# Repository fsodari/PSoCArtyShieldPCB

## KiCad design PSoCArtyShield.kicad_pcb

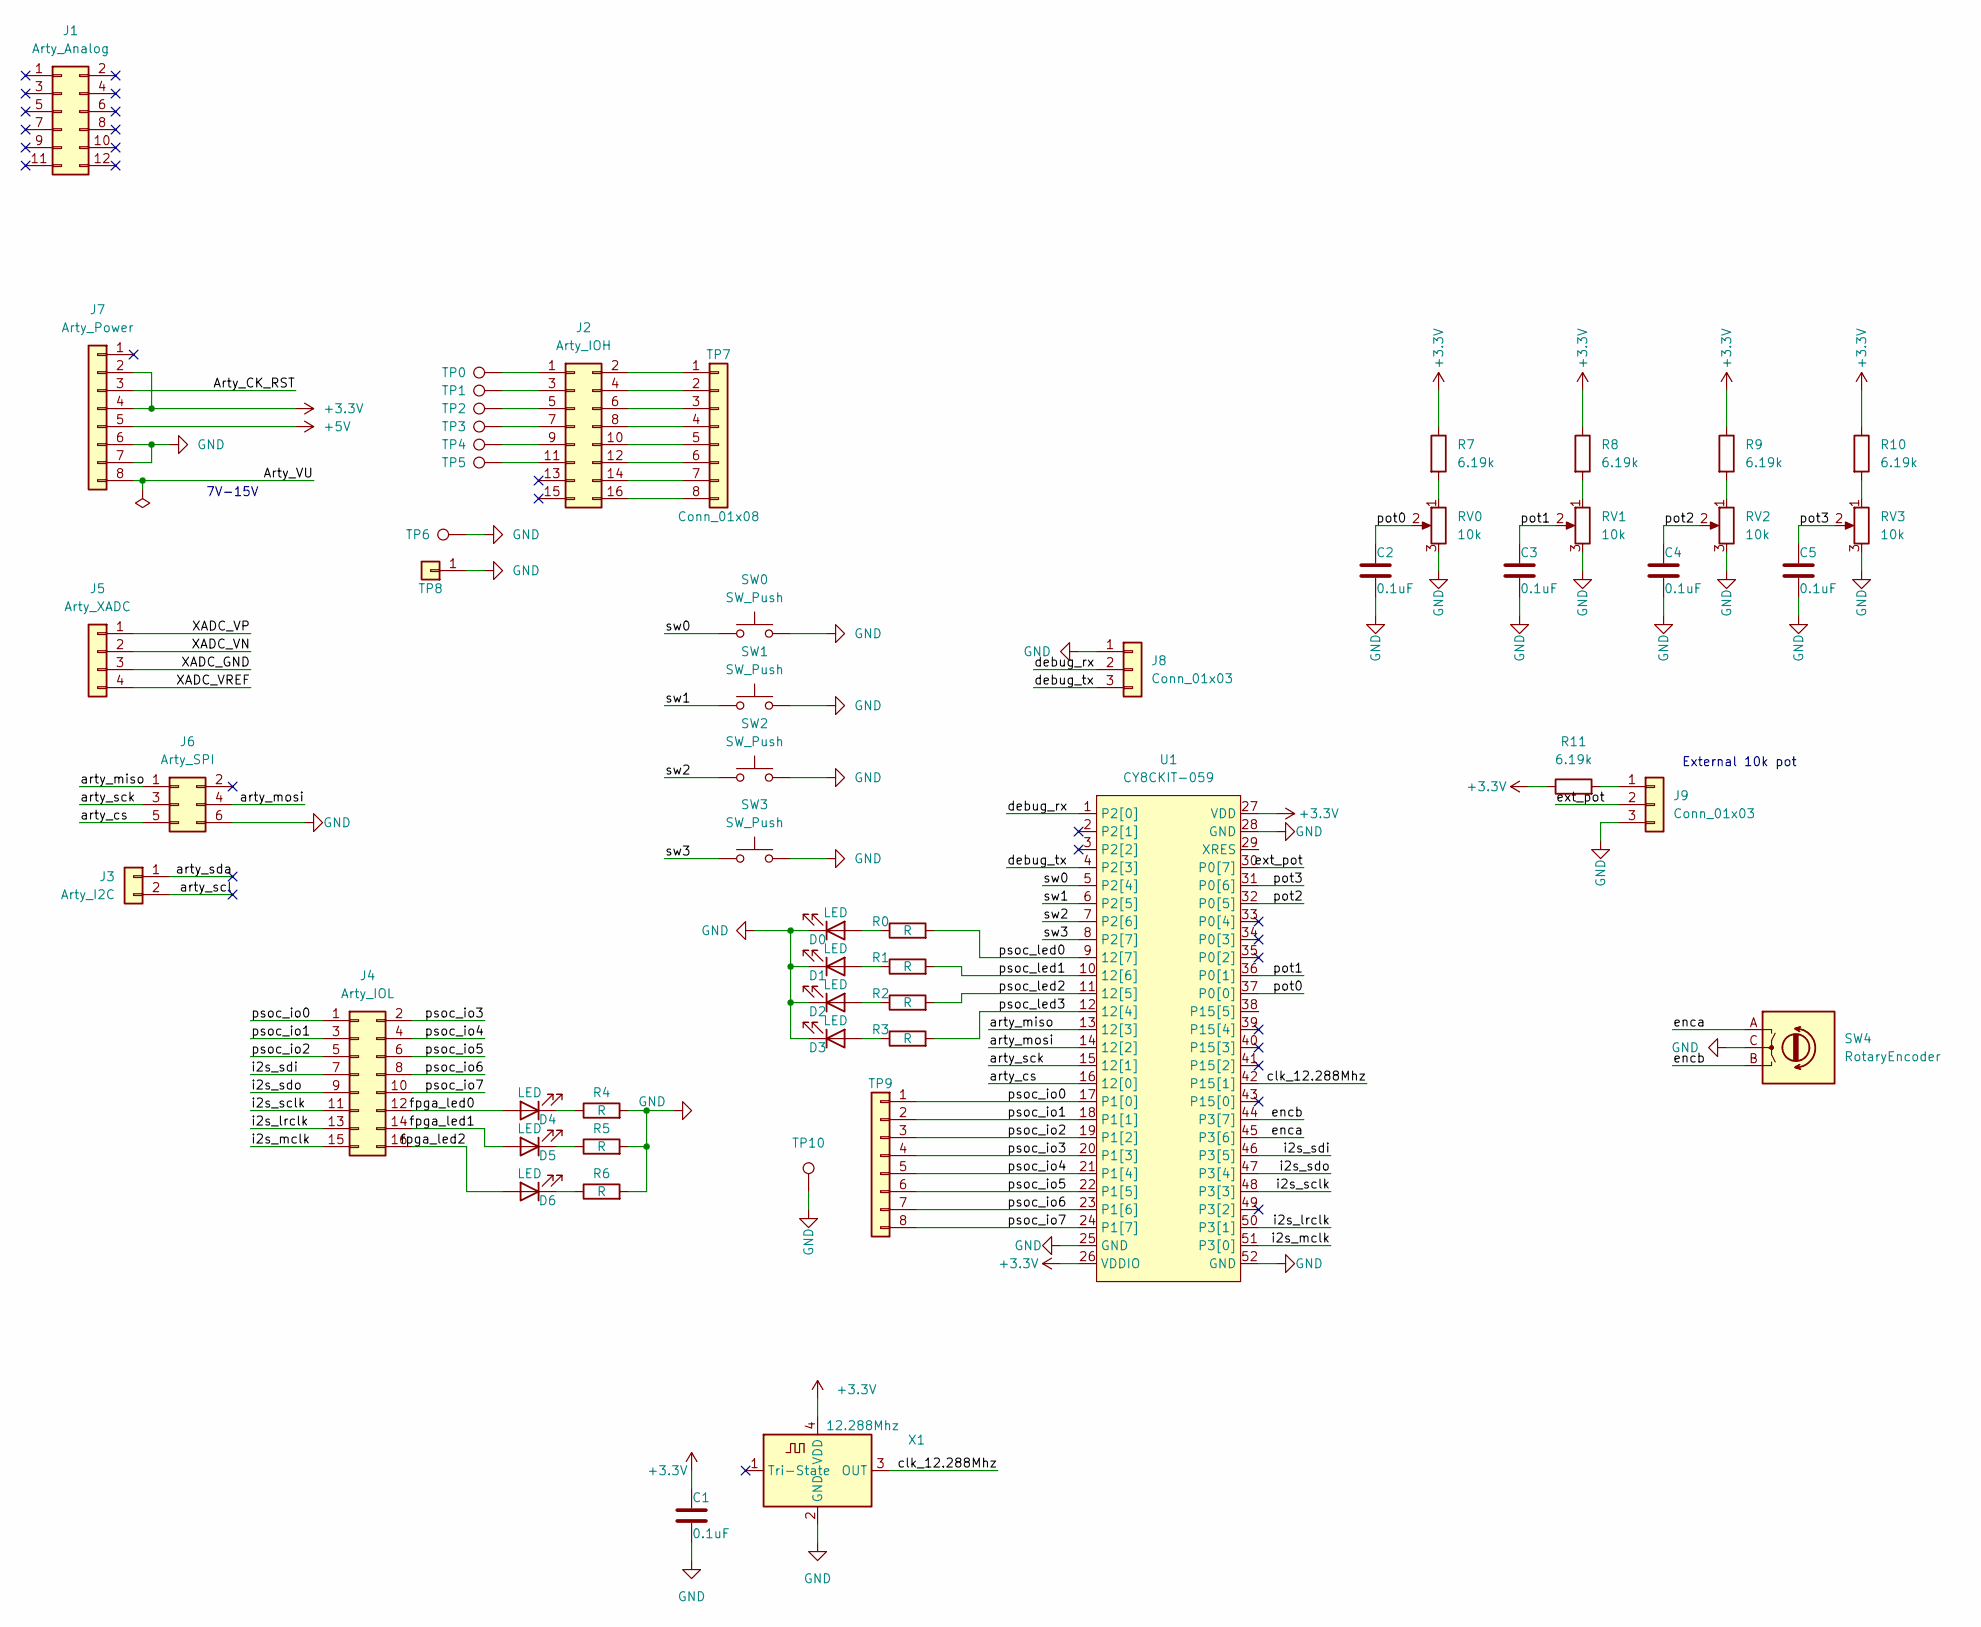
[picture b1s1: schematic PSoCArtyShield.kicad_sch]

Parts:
C1, C2, C3, C4, C5: 0.1uF; C_0402_1005Metric_Pad0.74x0.62mm_HandSolder
D0, D1, D2, D3, D4, D5, D6: LED; LED_0603_1608Metric_Pad1.05x0.95mm_HandSolder
J1: Arty_Analog; PinHeader_2x06_P2.54mm_Vertical
J2: Arty_IOH; PinHeader_2x08_P2.54mm_Vertical
J3: Arty_I2C; PinHeader_1x02_P2.54mm_Vertical
J4: Arty_IOL; PinHeader_2x08_P2.54mm_Vertical
J5: Arty_XADC; PinHeader_2x02_P2.54mm_Vertical
J6: Arty_SPI; PinHeader_2x03_P2.54mm_Vertical
J7: Arty_Power; PinHeader_1x08_P2.54mm_Vertical
J8, J9: Conn_01x03; PinHeader_1x03_P2.54mm_Vertical
R0, R1, R2, R3, R4, R5, R6: R; R_0603_1608Metric_Pad0.98x0.95mm_HandSolder
R7, R8, R9, R10, R11: 6.19k; R_0603_1608Metric_Pad0.98x0.95mm_HandSolder
RV0, RV1, RV2, RV3: 10k; Potentiometer_Bourns_PTV09A-1_Single_Vertical
SW0, SW1, SW2, SW3: SW_Push; SW_PUSH-12mm_Wuerth-430476085716
SW4: RotaryEncoder; RotaryEncoder_Alps_EC11E_Vertical_H20mm
TP0, TP1, TP2, TP3, TP4, TP5, TP6, TP10: TestPoint_Keystone_5019_Minature
TP7: Conn_01x08; PinHeader_1x08_P2.54mm_Vertical
TP8: PinHeader_1x01_P2.54mm_Vertical
TP9: PinHeader_1x08_P2.54mm_Vertical
U1: CY8CKIT-059
X1: 12.288Mhz; Oscillator_SMD_ECS_2520MV-xxx-xx-4Pin_2.5x2.0mm

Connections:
+3V3: C1.1, J7.2, J7.4, R7.1, R8.1, R9.1, R10.1, R11.1, U1.26 (VDDIO), U1.27 (VDD), X1.4 (VDD)
+5V: J7.5
/Arty_CK_RST: J7.3
/Arty_VU: J7.8
/XADC_GND: J5.3
/XADC_VN: J5.2
/XADC_VP: J5.1
/XADC_VREF: J5.4
/arty_cs: J6.5, U1.16 (12[0])
/arty_miso: J6.1, U1.13 (12[3])
/arty_mosi: J6.4, U1.14 (12[2])
/arty_sck: J6.3, U1.15 (12[1])
/arty_scl: J3.2
/arty_sda: J3.1
/clk_12.288Mhz: U1.42 (P15[1]), X1.3 (OUT)
/debug_rx: J8.2, U1.1 (P2[0])
/debug_tx: J8.3, U1.4 (P2[3])
/enca: SW4.A, U1.45 (P3[6])
/encb: SW4.B, U1.44 (P3[7])
/ext_pot: J9.2, U1.30 (P0[7])
/fpga_led0: D4.2 (A), J4.12
/fpga_led1: D5.2 (A), J4.14
/fpga_led2: D6.2 (A), J4.16
/i2s_lrclk: J4.13, U1.50 (P3[1])
/i2s_mclk: J4.15, U1.51 (P3[0])
/i2s_sclk: J4.11, U1.48 (P3[3])
/i2s_sdi: J4.7, U1.46 (P3[5])
/i2s_sdo: J4.9, U1.47 (P3[4])
/pot0: C2.1, RV0.2, U1.37 (P0[0])
/pot1: C3.1, RV1.2, U1.36 (P0[1])
/pot2: C4.1, RV2.2, U1.32 (P0[5])
/pot3: C5.1, RV3.2, U1.31 (P0[6])
/psoc_io0: J4.1, TP9.1, U1.17 (P1[0])
/psoc_io1: J4.3, TP9.2, U1.18 (P1[1])
/psoc_io2: J4.5, TP9.3, U1.19 (P1[2])
/psoc_io3: J4.2, TP9.4, U1.20 (P1[3])
/psoc_io4: J4.4, TP9.5, U1.21 (P1[4])
/psoc_io5: J4.6, TP9.6, U1.22 (P1[5])
/psoc_io6: J4.8, TP9.7, U1.23 (P1[6])
/psoc_io7: J4.10, TP9.8, U1.24 (P1[7])
/psoc_led0: R0.2, U1.9 (12[7])
/psoc_led1: R1.2, U1.10 (12[6])
/psoc_led2: R2.2, U1.11 (12[5])
/psoc_led3: R3.2, U1.12 (12[4])
/sw0: SW0.1, U1.5 (P2[4])
/sw1: SW1.1, U1.6 (P2[5])
/sw2: SW2.1, U1.7 (P2[6])
/sw3: SW3.1, U1.8 (P2[7])
GND: C1.2, C2.2, C3.2, C4.2, C5.2, D0.1 (K), D1.1 (K), D2.1 (K), D3.1 (K), J6.6, J7.6, J7.7, J8.1, J9.3, R4.2, R5.2, R6.2, RV0.3, RV1.3, RV2.3, RV3.3, SW0.2, SW1.2, SW2.2, SW3.2, SW4.C, TP6.1, TP8.1, TP10.1, U1.25 (GND), U1.28 (GND), U1.52 (GND), X1.2 (GND)
unnamed: D0.2 (A), R0.1
unnamed: D1.2 (A), R1.1
unnamed: D2.2 (A), R2.1
unnamed: D3.2 (A), R3.1
unnamed: D4.1 (K), R4.1
unnamed: D5.1 (K), R5.1
unnamed: D6.1 (K), R6.1
unnamed: J2.1, TP0.1
unnamed: J2.2, TP7.1
unnamed: J2.3, TP1.1
unnamed: J2.4, TP7.2
unnamed: J2.5, TP2.1
unnamed: J2.6, TP7.3
unnamed: J2.7, TP3.1
unnamed: J2.8, TP7.4
unnamed: J2.9, TP4.1
unnamed: J2.10, TP7.5
unnamed: J2.11, TP5.1
unnamed: J2.12, TP7.6
unnamed: J2.14, TP7.7
unnamed: J2.16, TP7.8
unnamed: J9.1, R11.2
unnamed: R7.2, RV0.1
unnamed: R8.2, RV1.1
unnamed: R9.2, RV2.1
unnamed: R10.2, RV3.1

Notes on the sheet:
7V-15V
External 10k pot

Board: 2 copper layers, 55 parts (0 on the bottom side), 66 nets, no tracks yet.
